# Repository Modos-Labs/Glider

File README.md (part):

# Glider

Open-source Eink monitor with an emphasis on low latency.

Note: This repo only contains the hardware design, the gateware running on the FPGA is my open-source [Caster EPDC](https://gitlab.com/zephray/Caster/) design. This README also contains information about the Caster as well.

This is a long document, containing not just information about this project, but also pretty much everything I know about Eink. Given it's a bit hard to gather information about Eink online, I think this is the right thing to do. Use the following table of contents to navigate around.

Eink is a registered trademark and brand of E Ink Corporation. All the contents provided in this repo are based on publicly available information online and original research. They are not endorsed by Eink in any way and they may contain errors and/ or inaccuracies. 

If you're interested in attaining a board, checkout the [product page for the Modos Paper Dev Kit on Crowd Supply](https://www.crowdsupply.com/modos-tech/modos-paper-monitor). For complete monitor ready to be used out-of-the-box, checkout the [product page for the Modos Flow on Crowd Supply](https://www.crowdsupply.com/modos-tech/modos-flow).

If you are interested in Eink or any other display technologies, I have a Discord server for that. Feel free to join: [https://discord.gg/rtT7euSHQS](https://discord.gg/rtT7euSHQS) . (This Discord server is also not endorsed by Eink or any other company. It's not a customer support server.) For Modos product support or other inqueries about Modos products, use [https://discord.gg/6ktE6VxSyh](https://discord.gg/6ktE6VxSyh).

## Quick Start

If you already have a Glider board/ kit: For board setup, flashing, development build loops, and display configuration, start with [USAGE.md](USAGE.md).

## Table of Contents 

- [Overview](#overview)
    - [Features](#features)
    - [Hardware](#hardware)
    - [Components](#components)
- [Eink Screens](#eink-screens)
    - [Basic Theory of Operation](#basic-theory-of-operation)
    - [Advantages and Disadvantages](#advantages-and-disadvantages)
    - [The Role of Eink Controller](#the-role-of-eink-controller)
    - [Screen Panel Types](#screen-panel-types)
    - [Using Screen with Integrated Controller](#using-screen-with-integrated-controller)
    - [Using Screen without Integrated Controller](#using-screen-without-integrated-controller)
    - [Understanding Waveform](#understanding-waveform)
    - [Greyscale Display](#greyscale-display)
    - [Color Display](#color-display)
    - [Dithering](#dithering)
    - [Eink Screen Generations](#eink-screen-generations)
- [Caster/ Glider Design](#design-of-caster-and-glider)
    - [Low Latency Drive](#low-latency-drive)
    - [Hybrid Greyscale Mode](#hybrid-greyscale-mode)
    - [Limitations](#limitations)
    - [Hardware Design Decisions]()
    - [Gateware Architecture](#gateware-architecture)
    - [Firmware Functions](#firmware-functions)
    - [Resources Utilization](#resources-utilization)
- [Building](#building)
    - [PCB](#pcb)
    - [FPGA Bitstream](#fpga-bitstream)
    - [MCU Firmware](#mcu-firmware)
    - [Flashing Board](#flashing-board)
    - [Compatible Screens](#compatible-screens)
- [References](#references)
- [License](#license)
- [Appendix](#appendix)
    - [Using Screens without Datasheet](#using-screens-without-datasheet)
    - [Screen List](#screen-list)

## Overview

### Features

- Complete solution for low-latency/ high-refresh-rate EPD monitor
- Supports electrophoretic display panels with parallel I/F (Eink(R), OED and DES)
- Supports both monochrome and color-filter-array (such as Kaleido(TM)) based color screen
- Extremely low processing delay of \<20 us
- Supports binary, 4-level grayscale, and 16-level grayscale output modes
- Latency-optimized binary and 4-level grayscale driving modes
- Hybrid automatic binary and 16-level grayscale driving mode
- Host software runtime controllable regional update and mode switching
- Hardware bayer dithering, blue-noise dithering, and error-diffusion dithering with no additional latency
- Controller takes standard HVsync signal input
- Board-level design supports USB-C (USB Type-C DisplayPort Alt Mode) and DVI input

### Hardware

- Xilinx(R) Spartan-6 LX16 FPGA running Caster
- DDR3-800 framebuffer memory
- Type-C DisplayPort Alt-Mode video input with onboard PTN3460 DP-LVDS bridge or
- DVI (via miniHDMI connector) video input with onboard ADV7611 decoder
- Epaper power supply with up to 1A peak current on +/-15V rail supporting large panels
- VCOM kick-back voltage measurement support
- On-board STM32H750 microcontroller for USB communication and firmware upgrade
- Up to 133MP/s processing rate with error-diffusion dithering enabled, >200MP/s when disabled

The board is designed with KiCad. You may need the latest stable version of KiCad to open the source file.

### Components

This repo hosts the PCB design and firmware source code. The RTL code is in a separate repo: [https://gitlab.com/zephray/Caster/](https://gitlab.com/zephray/Caster/).

## Eink Screens

Eink is the brand of a family of paper-like electrophoretic displays. The underlying technology is invented in the MIT Media Lab between 1995 and 1997 by Barrett Comiskey, J.D. Albert, and Joseph Jacobson. They later founded the E Ink Corporation to commercialize this technology.

Nowadays they are commonly used on e-readers and electronic shelf labels. You’ve probably seen them on Kindle, in stores, or maybe in some train stations as well.

| eReader/ Tablets | Electronic Shelf Label | Digital Signage |
|-|-|-|
|  |  |  |

(Source: https://www.eink.com/application, image copyright Eink corporation)

This section gives an overview of the electrophoretic displays, including the screen panels available and underlying technology. Note this project doesn't and can't support all electrophoretic screens. This documentation also solely focuses on using existing off-the-shelf screen panels rather than the physics or manufacturing process of one.

### Basic Theory of Operation

In the simplest form, you have charged particles with different colors, dispersed in some oil in some transparent container. By applying electric fields the particles can be moved up or down to produce either black or white, or a mixture of that.

(Source: https://www.eink.com/tech/detail/How_it_works , copyright Eink Corporation)

There are multiple technologies based on this basic concept, namely Eink’s micro-capsule display, SiPix (now acquired by Eink)’s micro-cup display, and WFT’s DES display. They differ in specific ways of confining the particles in containers, but otherwise very similar.

The pixels on the screen are typically arranged as a 2D array, driven with TFTs. The pixels are scanned/ driven periodically at a fixed refresh rate, typically ranging from 50Hz to 120Hz. Applying positive voltage on the pixel will typically drive the particles toward the white state while applying negative voltage will drive the particles towards the black state. This is similar to active matrix TN/IPS LCDs, which also use 2D TFT arrays and electrical fields for changing state. However, unlike LCDs, EPDs maintain their state after the electrical field is removed. So unlike LCDs which require continuous refreshing, the EPDs only need to be refreshed till the pixels are fully driven.

In terms of driving the screen panel, depending on the pixel value (1 or 0), each pixel would be driven either with a positive voltage or a negative voltage. A global counter can be used to count the frames elapsed and stop driving the pixels after a predefined period of time (for example, 100ms). Two framebuffers are typically used for determining if the pixel has changed color or not. If not, then the pixel does not need to be driven.

### Advantages and Disadvantages

In terms of display quality, EPDs are no match for modern IPS LCDs. The following is a comparison table of key parameters. The specific number would vary depending on the screen used but should be within the same ballpark.

| | Monochrome EPD | CFA-based Color EPD | Transmissive TFT IPS LCD | Reflective TFT TN LCD |
|-|-|-|-|-|
| Contrast Ratio | ~17:1 | ~14:1 | ~1000:1 | ~14:1 |
| Colors | 16 (Greyscale) | 4096 | 16M | 256 |
| Color Gamut | N/A | ~1.5% sRGB | ~99.9% sRGB | N/A |
| Reflectivity | ~45% | ~25% | N/A | ~15% |
| Response Time | ~150ms | ~150ms | ~10ms | ~15ms |

It has a few advantages. It reflects lights instead of emitting lights, so it generally consumes less power and can be used outdoors, etc. It’s also bistable, which means that it retains the image after the power has been removed. Personally, the biggest differentiating factor for me (author of this README) is that it looks like paper.

The image above shows a comparison between reflective TFT LCD (SHARP memory LCD in this case) and Eink. The LCD has a mirror-like texture which changes reflectivity drastically in different angles, while the Eink is more paper-like.

| ZBD LCD | Ch LCD | STN LCD |
|-|-|-|
|  |  |  |
| Bistable, reflective, high contrast, no greyscale, ~10s refresh | Bistable, reflective, lower contrast, up to 32 level greyscale, ~5s refresh | Volatile, reflective, lower contrast, up to 32 level greyscale, ~100ms response |

There are many other reflective or bistable display technologies. They are all interesting displays on their own, but none of them feels like paper (yet).

Overall, there is no single perfect display technology. Each has its own unique strength. Pick the right one for your project.

### The Role of Eink Controller

The Eink controller is in some ways similar to the display controller (DC/ CRTC) + timing controller (TCON) in a typical LCD-based system. It takes the raw image data and converts it to signals required to drive the screen.

To understand the actual work of an eink controller, start from the basic concept. The color of a pixel can be changed by applying positive or negative voltage for a finite period of time. From the controller’s perspective, depending on the current state of the pixel and the desired state of the pixel, there are 4 possibilities.

| Current State | Target State | Action |
|-|-|-|
| Black | Black | No operation |
| Black | White | Apply positive voltage |
| White | Black | Apply negative voltage |
| White | White | No operation |

The controller needs to store and maintain the screen state inside of its own buffer memory, so it would typically have a large on-chip SRAM or an off-chip SDRAM controller. The controller should also have a timer to ensure the screen doesn't get overdriven or underdriven.

The controller often uses the so-called "[waveform](#understanding-waveform)" to replace the action column of the previous table. Instead of hardcoding the action for state transition, the actions are stored into a look-up-table (LUT) which can be modified at runtime to allow higher flexibility.

Controllers may also offer more advanced features such as [dithering](#dithering) acceleration, multiple region updates, automatic LUT selection, etc.

### Screen Panel Types

As discussed in the previous section, an Eink screen needs to be coupled to an Eink controller to function. Aside from that, the screen also needs high-voltage drivers to drive the TFTs and the pixels. Virtually all E-paper panels use either COG (Chip-on-Glass) or TAB (Tape Auto Bonding) to integrate some chips onto the screen panel itself. Most of the screens available today can be divided into two categories based on whether or not the controller is integrated in:

Here is a non-exhaustive list of the types based on their size: (the size or resolution is not related to or limited by the type, it is just for a certain size, and the vendors tend to make them the same type.)

- Screens without controller: 4.3", 6.0", 7.8", 8.0", 9.7", 10.3", 13.3", 25.3", 31.2", 42"
- Screens with controller: 1.02", 1.54", 2.13", 2.6", 2.9", 3.71", 4.2", 5.65", 5.83", 7.5", 12.48"

One may notice that almost all e-readers/ e-ink cellphones use screens without controllers, while almost all e-ink electronic shelf labels (ESL) use screens with controllers. This gives some hints about the advantages and disadvantages of two types:

| | Without Controller | With Controller |
|-|-|-|
| System Cost | High. A dedicated controller or SoC with an integrated controller is usually required. Needs a dedicated power supply. | Low. Virtually any MCU could drive the screen directly, and the power supply is integrated in. |
| Greyscale Levels | Generally 16 (4bpp), up to 32 (5bpp) | Generally 2 (BW only) or 4 (2bpp), with some hack, up to 16 (4bpp) |
| Refresh Speed | Generally fast (100ms~300ms) for BW. Depends on the screen used and the system architecture | Generally fast (100ms~300ms) for BW if the partial refresh is enabled. Greyscales are much slower, BWR or BWY screens would be even slower.
| Total Update Latency | Generally the same as refresh time. Depends on the system architecture | Slow. Ranging from 100ms to several seconds based on the resolution. |

Please keep in mind the discussion is about off-the-shelf screens you can buy today. These tradeoffs do not necessarily come from the fact the controller is integrated or not.

Note that I mentioned the refresh speed and total update latency. They are different:

The refresh speed refers to the time it takes to start refreshing the screen: from starting to seeing screen changing, to the screen finish showing the new content.

The total update latency refers to the latency when the processor needs to update the screen, to the screen finish showing the new content. As you can see, this is the biggest issue for screens with controllers. This is the main reason why they are rarely used on e-readers cell phones or PC monitors.

This diagram illustrates the difference between the two. It should be noted that the screens without controllers have the flexibility to be driven quickly, but the system designer might not architect the system for low latency.

### Using Screen with Integrated Controller

Screens with integrated controllers have almost everything already integrated. Common display panels of this type only need a few external capacitors, inductors, and MOSFETs to support the integrated bipolar power supply circuit, then it could be hooked up to MCUs or MPUs using common interfaces like SPI or I2C. There are a lot of driving boards and examples of these screens available online.

To be expanded (TODO)

### Using Screen without Integrated Controller

This could get complicated. Note I used a lot of "generally" in the previous comparison table because there are many things one could do to drive them. Some of them would certainly impact the performance. The main issue here is the controller chip. There are three solutions to drive these screens:

- Using a dedicated controller chip to drive the screen
- Using an SoC that has an integrated controller
- Using a fast MCU/SoC to emulate the controller with GPIO (software timing controller)

Then, again here is a comparison between them:

| | Specialized controller chip | SoC with integrated controller | MCU + Software TCON |
|-|-|-|-|
| Resolution | UXGA+ | UXGA+ | Limited by MCU RAM. Up to XGA with SRAM, UXGA with PSRAM, UXGA+ with DDR |
| Greyscale | Up to 32 | Up to 32 | Up to 32 |
| Partial Update | Yes | Yes | Yes |
| Total Update Latency | Depends. Could be very close to refresh speed, could be slow like screens with controller | Same as refresh speed | Same as refresh speed if data is internally generated (not streaming from an external device such as a PC) |
| Suitable Applications | IoT devices, E-readers, cellphones, E-ink monitors. possibly E-ink laptops | Advanced IoT devices, E-readers, cellphones, E-ink typewriters, possibly lower performance E-ink laptops | When using MCU: IoT devices, large ESLs, simple DIY E-readers. When using MPU: Same as SoC with integrated controller |

When using a dedicated controller, it could accept data from external devices. This allows it to be used in various different types of applications. Ranging from IoT devices, and ESLs, to PC monitors with relatively fast refresh rate and low latency.

When using SoC or MCU, the display content is generated by the SoC or MCU itself, which ultimately is limited by the capability of the SoC or MCU. Given the current SoCs with E-ink display controllers are usually limited in performance, the application is limited. The same goes for MCU, it does what an MCU could do. You could find ways to stream video data into SoC or MCUs by using USB, camera interface, WiFi, etc., but this might not be optimal.

#### Existing Solutions

- Specialized controller chip
    - Closed-source
        - EPSON S1D13xxx: Widely used EPD controller in early E-readers. Proprietary, no documents available. Probably EOL.
        - IT8951: Used on the waveshare EPD Hat. Documents are available. It works with large EPDs up to 2048x2048. The drawback is the speed as the interface between processor and IT8951 could be slow. This is similar to the situation on screens with integrated controller
        - T1000: Also known as IT8957, upgraded model of IT8951. It supports even higher resolution. It features a higher speed MIPI DSI interface to mitigate the slow speed of IT8951. Features an integrated OpenRISC based processor.
        - T2000: Upgraded model of T1000.
        - T2001: Also known as IT8959. Features an integrated RISC-V based processor. Works with large EPDs up to 2560x1920. Supports SPI, RGB, MIPI DSI interface.
        - Waveshare HDMI driver board: FPGA-based controller. Closed source but easily purchasable, could be integrated into larger projects as a module.
    - Open-source
        - This project (Caster + Glider): FPGA-based controller, multiple update modes, ultra-low latency processing, and wide range of screen support.
        - https://hackaday.io/project/21607-paperback-a-desktop-epaper-monitor: FPGA-based controller. However, doesn't support partial update mode and slower speed.
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
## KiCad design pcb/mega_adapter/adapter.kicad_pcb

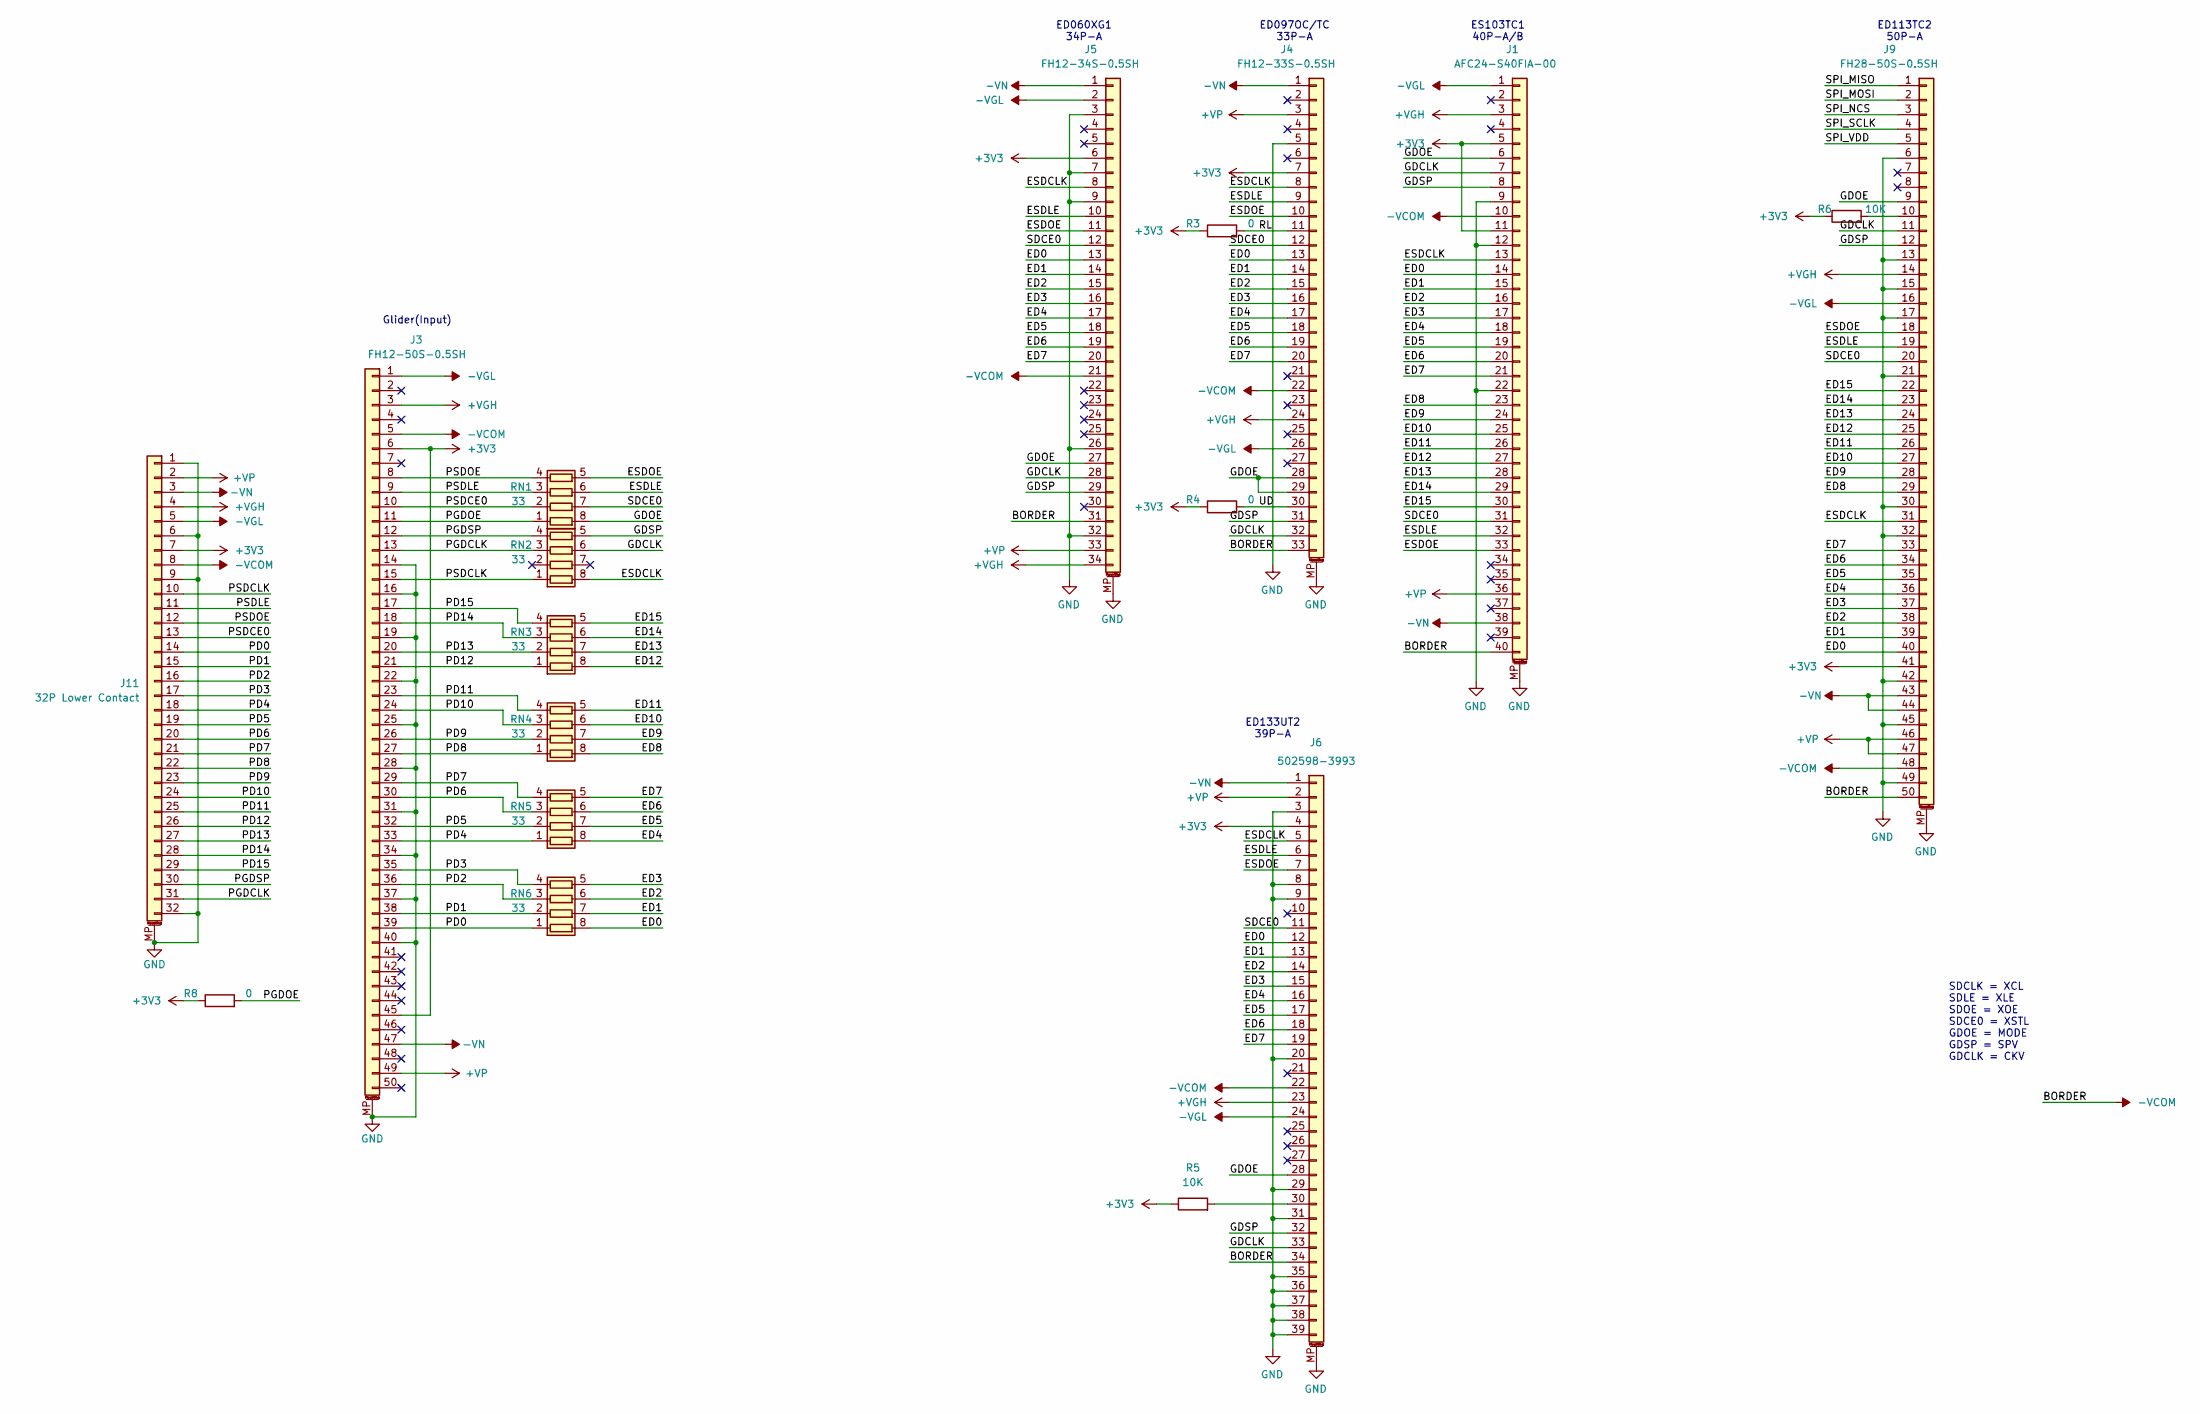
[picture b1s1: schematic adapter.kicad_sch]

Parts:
J1: AFC24-S40FIA-00; Omron_XF2M-4015-1A_1x40-1MP_P0.5mm_Horizontal
J3: FH12-50S-0.5SH; Hirose_FH12-50S-0.5SH_1x50-1MP_P0.50mm_Horizontal_Mirrored
J4: FH12-33S-0.5SH; Hirose_FH12-33S-0.5SH_1x33-1MP_P0.50mm_Horizontal
J5: FH12-34S-0.5SH; Hirose_FH12-34S-0.5SH_1x34-1MP_P0.50mm_Horizontal
J6: 502598-3993; Molex_5025983993; LCSC 609-10064555-392120HLFCT-ND
J9: FH28-50S-0.5SH; Hirose_FH12-50S-0.5SH_1x50-1MP_P0.50mm_Horizontal
J11: 32P Lower Contact; Hirose_FH12-32S-0.5SH_1x32-1MP_P0.50mm_Horizontal_Mirrored
R3, R4, R8: 0; R_0402_1005Metric
R5, R6: 10K; R_0402_1005Metric
RN1, RN2, RN3, RN4, RN5, RN6: 33; R_Array_Convex_4x0402

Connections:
+3V3: J1.5, J1.11, J3.6, J3.45, J4.7, J5.6, J6.4, J9.41, J11.7, R3.1, R4.1, R5.1, R6.1, R8.1
+VGH: J1.3, J3.3, J4.24, J5.34, J6.23, J9.14, J11.4
+VP: J1.36, J3.49, J4.3, J5.33, J6.2, J9.46, J9.47, J11.2
-VCOM: J1.10, J1.40, J3.5, J4.22, J4.33, J5.21, J5.31, J6.22, J6.34, J9.48, J9.50, J11.8
-VGL: J1.1, J3.1, J4.26, J5.2, J6.24, J9.16, J11.5
-VN: J1.38, J3.47, J4.1, J5.1, J6.1, J9.43, J9.44, J11.3
/ED0: J1.14, J4.13, J5.13, J6.12, J9.40, RN6.8 (R1.2)
/ED1: J1.15, J4.14, J5.14, J6.13, J9.39, RN6.7 (R2.2)
/ED2: J1.16, J4.15, J5.15, J6.14, J9.38, RN6.6 (R3.2)
/ED3: J1.17, J4.16, J5.16, J6.15, J9.37, RN6.5 (R4.2)
/ED4: J1.18, J4.17, J5.17, J6.16, J9.36, RN5.8 (R1.2)
/ED5: J1.19, J4.18, J5.18, J6.17, J9.35, RN5.7 (R2.2)
/ED6: J1.20, J4.19, J5.19, J6.18, J9.34, RN5.6 (R3.2)
/ED7: J1.21, J4.20, J5.20, J6.19, J9.33, RN5.5 (R4.2)
/ED8: J1.23, J9.29, RN4.8 (R1.2)
/ED9: J1.24, J9.28, RN4.7 (R2.2)
/ED10: J1.25, J9.27, RN4.6 (R3.2)
/ED11: J1.26, J9.26, RN4.5 (R4.2)
/ED12: J1.27, J9.25, RN3.8 (R1.2)
/ED13: J1.28, J9.24, RN3.7 (R2.2)
/ED14: J1.29, J9.23, RN3.6 (R3.2)
/ED15: J1.30, J9.22, RN3.5 (R4.2)
/ESDCLK: J1.13, J4.8, J5.8, J6.5, J9.31, RN2.8 (R1.2)
/ESDLE: J1.32, J4.9, J5.10, J6.6, J9.19, RN1.6 (R3.2)
/ESDOE: J1.33, J4.10, J5.11, J6.7, J9.18, RN1.5 (R4.2)
/GDCLK: J1.7, J4.32, J5.28, J6.33, J9.11, RN2.6 (R3.2)
/GDOE: J1.6, J4.28, J4.29, J5.27, J6.28, J9.9, RN1.8 (R1.2)
/GDSP: J1.8, J4.31, J5.29, J6.32, J9.12, RN2.5 (R4.2)
/PD0: J3.39, J11.14, RN6.1 (R1.1)
/PD1: J3.38, J11.15, RN6.2 (R2.1)
/PD2: J3.36, J11.16, RN6.3 (R3.1)
/PD3: J3.35, J11.17, RN6.4 (R4.1)
/PD4: J3.33, J11.18, RN5.1 (R1.1)
/PD5: J3.32, J11.19, RN5.2 (R2.1)
/PD6: J3.30, J11.20, RN5.3 (R3.1)
/PD7: J3.29, J11.21, RN5.4 (R4.1)
/PD8: J3.27, J11.22, RN4.1 (R1.1)
/PD9: J3.26, J11.23, RN4.2 (R2.1)
/PD10: J3.24, J11.24, RN4.3 (R3.1)
/PD11: J3.23, J11.25, RN4.4 (R4.1)
/PD12: J3.21, J11.26, RN3.1 (R1.1)
/PD13: J3.20, J11.27, RN3.2 (R2.1)
/PD14: J3.18, J11.28, RN3.3 (R3.1)
/PD15: J3.17, J11.29, RN3.4 (R4.1)
/PGDCLK: J3.13, J11.31, RN2.3 (R3.1)
/PGDOE: J3.11, R8.2, RN1.1 (R1.1)
/PGDSP: J3.12, J11.30, RN2.4 (R4.1)
/PSDCE0: J3.10, J11.13, RN1.2 (R2.1)
/PSDCLK: J3.15, J11.10, RN2.1 (R1.1)
/PSDLE: J3.9, J11.11, RN1.3 (R3.1)
/PSDOE: J3.8, J11.12, RN1.4 (R4.1)
/RL: J4.11, R3.2
/SDCE0: J1.31, J4.12, J5.12, J6.11, J9.20, RN1.7 (R2.2)
/SPI_MISO: J9.1
/SPI_MOSI: J9.2
/SPI_NCS: J9.3
/SPI_SCLK: J9.4
/SPI_VDD: J9.5
/UD: J4.30, R4.2
GND: J1.9, J1.12, J1.22, J1.MP (MountPin), J3.14, J3.16, J3.19, J3.22, J3.25, J3.28, J3.31, J3.34, J3.37, J3.40, J3.MP (MountPin), J4.5, J4.MP (MountPin), J5.3, J5.7, J5.9, J5.26, J5.32, J5.MP (MountPin), J6.3, J6.8, J6.9, J6.20, J6.29, J6.31, J6.35, J6.36, J6.37, J6.38, J6.39, J6.MP (MountPin), J9.6, J9.13, J9.15, J9.17, J9.21, J9.30, J9.32, J9.42, J9.45, J9.49, J9.MP (MountPin), J11.1, J11.6, J11.9, J11.32, J11.MP (MountPin)
unnamed: J6.30, R5.2
unnamed: J9.10, R6.2

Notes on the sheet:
ED133UT2 39P-A
ED060XG1 34P-A
ED113TC2 50P-A
Glider(Input)
ES103TC1 40P-A/B
ED097OC/TC 33P-A
SDCLK = XCL SDLE = XLE SDOE = XOE SDCE0 = XSTL GDOE = MODE GDSP = SPV GDCLK = CKV

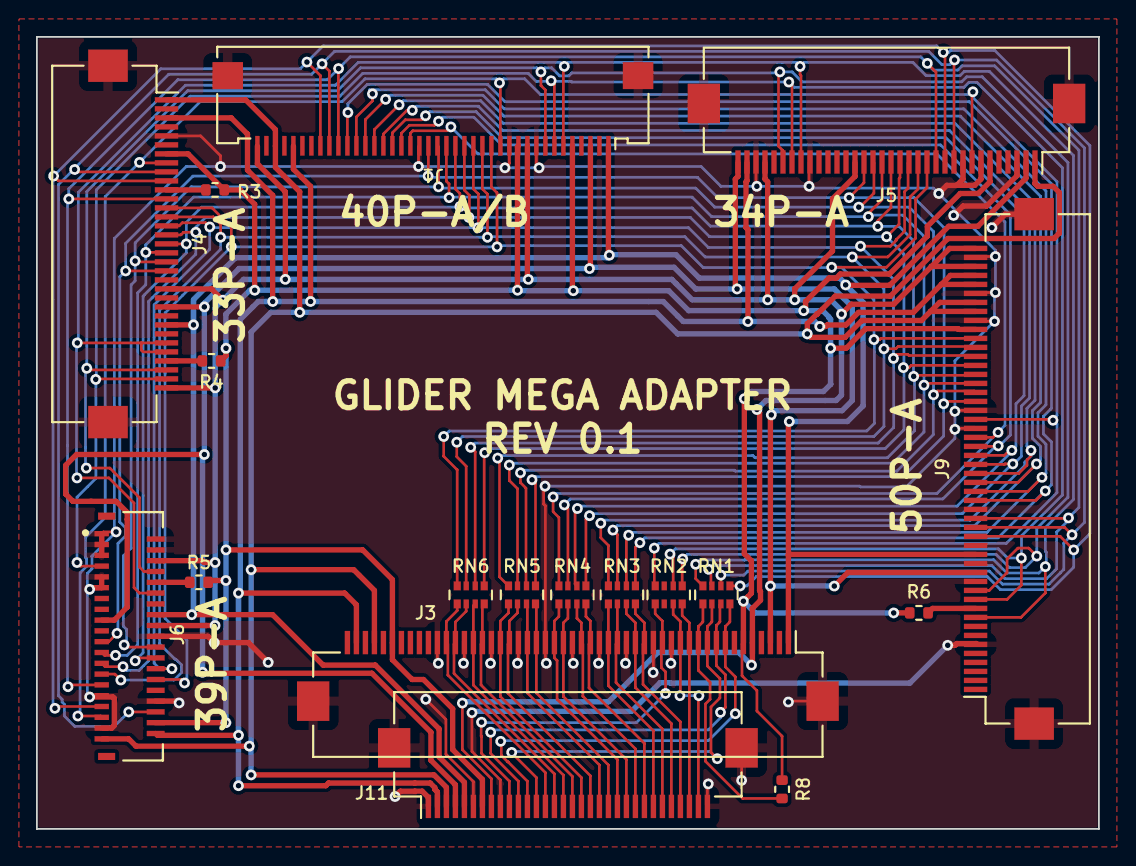
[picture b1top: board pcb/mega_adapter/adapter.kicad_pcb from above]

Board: 2 copper layers, 59.0 x 44.0 mm, 18 parts (0 on the bottom side), 57 nets.

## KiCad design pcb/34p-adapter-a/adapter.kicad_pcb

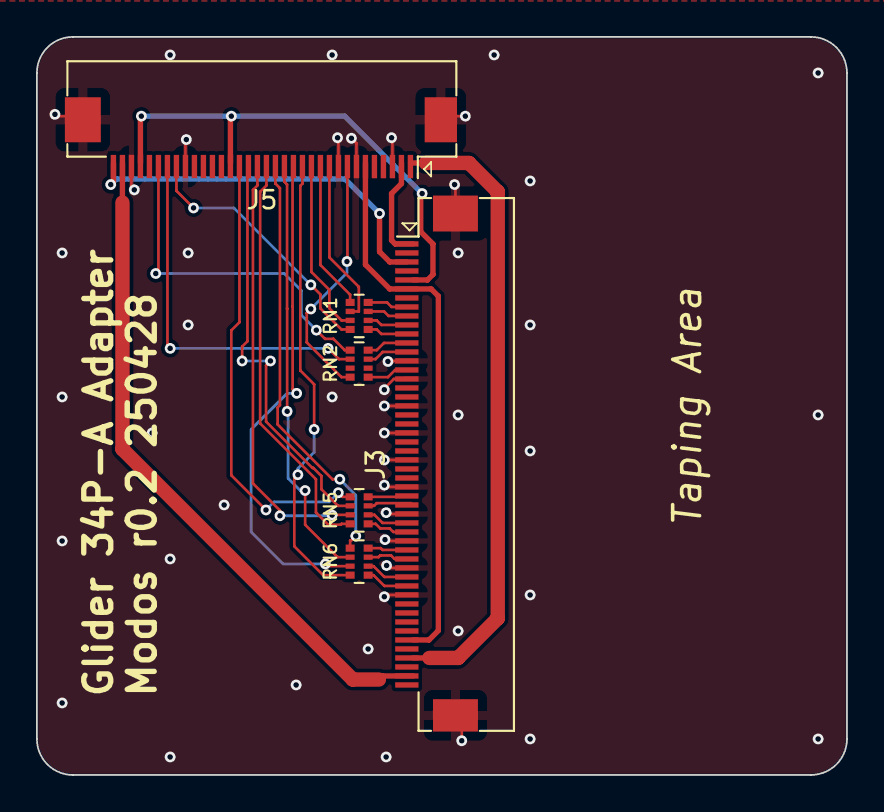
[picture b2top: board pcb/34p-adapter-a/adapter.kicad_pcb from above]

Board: 2 copper layers, 45.0 x 41.0 mm, 6 parts (0 on the bottom side), 37 nets.

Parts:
J3: FH12-50S-0.5SH; Xunpu_FPC-05F-50PH20_1x50-1MP_P0.50mm_Horizontal_Mirrored
J5: FH12-34S-0.5SH; Xunpu_FPC-05F-34PH20_1x34-1MP_P0.50mm_Horizontal
RN1, RN2, RN5, RN6: 33; R_Array_Convex_4x0402

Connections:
+3V3: J3.6, J3.45, J5.6
+VGH: J3.3, J5.34
+VP: J3.49, J5.33
-VCOM: J3.5, J5.21, J5.31
-VGL: J3.1, J5.2
-VN: J3.47, J5.1
/ED0: J5.13, RN6.8 (R1.2)
/ED1: J5.14, RN6.7 (R2.2)
/ED2: J5.15, RN6.6 (R3.2)
/ED3: J5.16, RN6.5 (R4.2)
/ED4: J5.17, RN5.8 (R1.2)
/ED5: J5.18, RN5.7 (R2.2)
/ED6: J5.19, RN5.6 (R3.2)
/ED7: J5.20, RN5.5 (R4.2)
/ESDCLK: J5.8, RN2.8 (R1.2)
/ESDLE: J5.10, RN1.6 (R3.2)
/ESDOE: J5.11, RN1.5 (R4.2)
/GDCLK: J5.28, RN2.6 (R3.2)
/GDOE: J5.27, RN1.8 (R1.2)
/GDSP: J5.29, RN2.5 (R4.2)
/PD0: J3.39, RN6.1 (R1.1)
/PD1: J3.38, RN6.2 (R2.1)
/PD2: J3.36, RN6.3 (R3.1)
/PD3: J3.35, RN6.4 (R4.1)
/PD4: J3.33, RN5.1 (R1.1)
/PD5: J3.32, RN5.2 (R2.1)
/PD6: J3.30, RN5.3 (R3.1)
/PD7: J3.29, RN5.4 (R4.1)
/PGDCLK: J3.13, RN2.3 (R3.1)
/PGDOE: J3.11, RN1.1 (R1.1)
/PGDSP: J3.12, RN2.4 (R4.1)
/PSDCE0: J3.10, RN1.2 (R2.1)
/PSDCLK: J3.15, RN2.1 (R1.1)
/PSDLE: J3.9, RN1.3 (R3.1)
/PSDOE: J3.8, RN1.4 (R4.1)
/SDCE0: J5.12, RN1.7 (R2.2)
GND: J3.14, J3.16, J3.19, J3.22, J3.25, J3.28, J3.31, J3.34, J3.37, J3.40, J3.MP (MountPin), J5.3, J5.7, J5.9, J5.26, J5.32, J5.MP (MountPin)

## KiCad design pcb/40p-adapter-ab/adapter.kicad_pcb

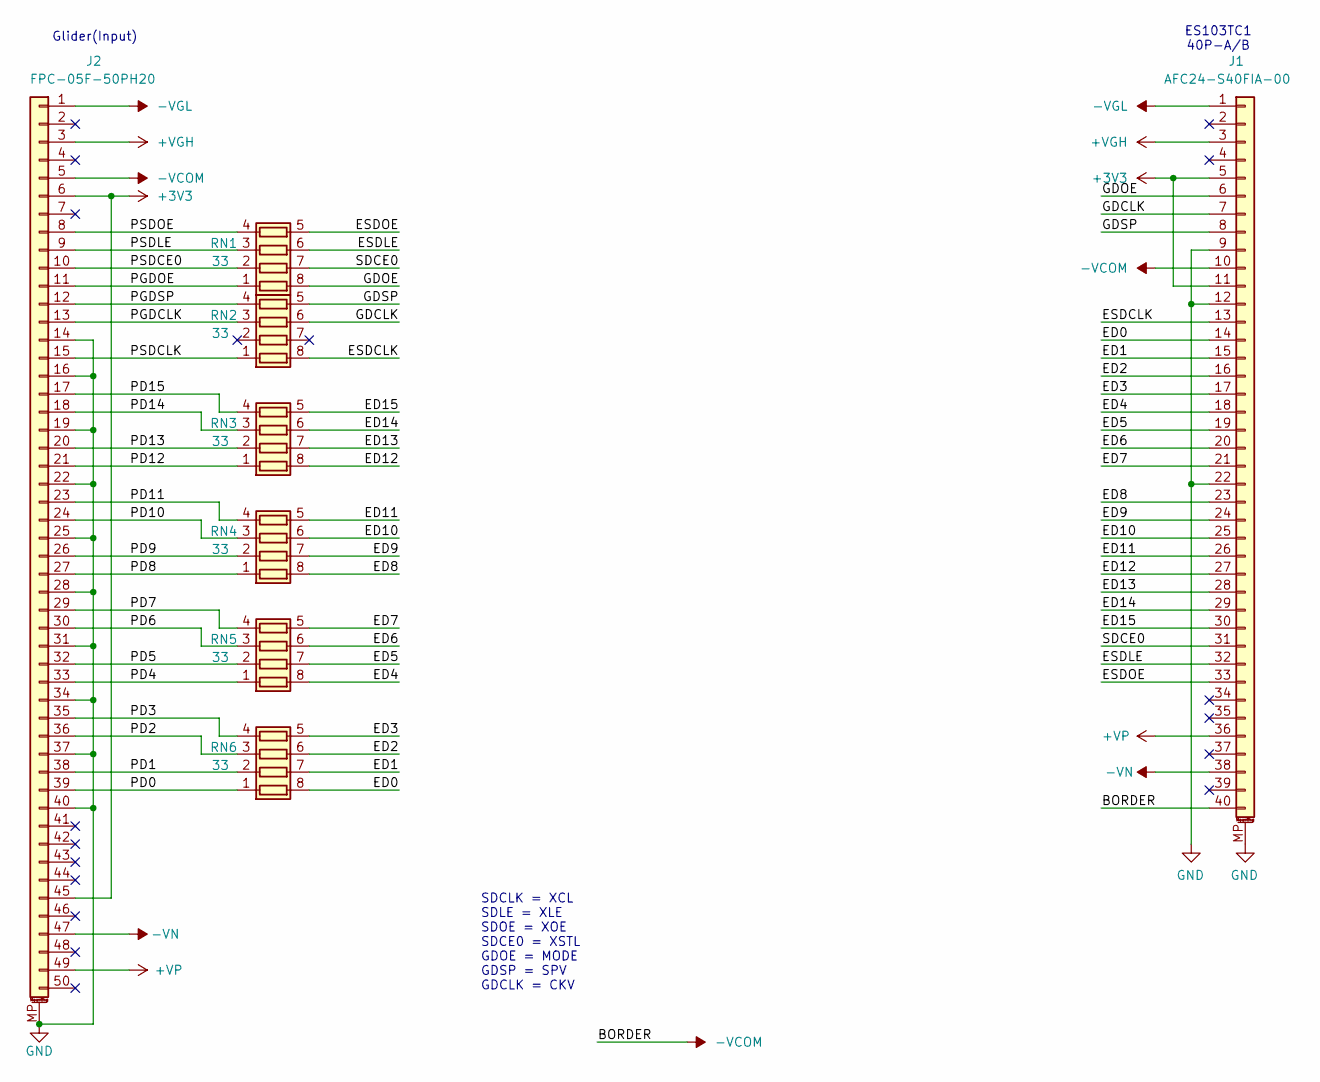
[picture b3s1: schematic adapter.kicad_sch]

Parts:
J1: AFC24-S40FIA-00; Omron_XF2M-4015-1A_1x40-1MP_P0.5mm_Horizontal
J2: FPC-05F-50PH20; Xunpu_FPC-05F-50PH20_1x50-1MP_P0.50mm_Horizontal_Mirrored
RN1, RN2, RN3, RN4, RN5, RN6: 33; R_Array_Convex_4x0402

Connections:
+3V3: J1.5, J1.11, J2.6, J2.45
+VGH: J1.3, J2.3
+VP: J1.36, J2.49
-VCOM: J1.10, J1.40, J2.5
-VGL: J1.1, J2.1
-VN: J1.38, J2.47
/ED0: J1.14, RN6.8 (R1.2)
/ED1: J1.15, RN6.7 (R2.2)
/ED2: J1.16, RN6.6 (R3.2)
/ED3: J1.17, RN6.5 (R4.2)
/ED4: J1.18, RN5.8 (R1.2)
/ED5: J1.19, RN5.7 (R2.2)
/ED6: J1.20, RN5.6 (R3.2)
/ED7: J1.21, RN5.5 (R4.2)
/ED8: J1.23, RN4.8 (R1.2)
/ED9: J1.24, RN4.7 (R2.2)
/ED10: J1.25, RN4.6 (R3.2)
/ED11: J1.26, RN4.5 (R4.2)
/ED12: J1.27, RN3.8 (R1.2)
/ED13: J1.28, RN3.7 (R2.2)
/ED14: J1.29, RN3.6 (R3.2)
/ED15: J1.30, RN3.5 (R4.2)
/ESDCLK: J1.13, RN2.8 (R1.2)
/ESDLE: J1.32, RN1.6 (R3.2)
/ESDOE: J1.33, RN1.5 (R4.2)
/GDCLK: J1.7, RN2.6 (R3.2)
/GDOE: J1.6, RN1.8 (R1.2)
/GDSP: J1.8, RN2.5 (R4.2)
/PD0: J2.39, RN6.1 (R1.1)
/PD1: J2.38, RN6.2 (R2.1)
/PD2: J2.36, RN6.3 (R3.1)
/PD3: J2.35, RN6.4 (R4.1)
/PD4: J2.33, RN5.1 (R1.1)
/PD5: J2.32, RN5.2 (R2.1)
/PD6: J2.30, RN5.3 (R3.1)
/PD7: J2.29, RN5.4 (R4.1)
/PD8: J2.27, RN4.1 (R1.1)
/PD9: J2.26, RN4.2 (R2.1)
/PD10: J2.24, RN4.3 (R3.1)
/PD11: J2.23, RN4.4 (R4.1)
/PD12: J2.21, RN3.1 (R1.1)
/PD13: J2.20, RN3.2 (R2.1)
/PD14: J2.18, RN3.3 (R3.1)
/PD15: J2.17, RN3.4 (R4.1)
/PGDCLK: J2.13, RN2.3 (R3.1)
/PGDOE: J2.11, RN1.1 (R1.1)
/PGDSP: J2.12, RN2.4 (R4.1)
/PSDCE0: J2.10, RN1.2 (R2.1)
/PSDCLK: J2.15, RN2.1 (R1.1)
/PSDLE: J2.9, RN1.3 (R3.1)
/PSDOE: J2.8, RN1.4 (R4.1)
/SDCE0: J1.31, RN1.7 (R2.2)
GND: J1.9, J1.12, J1.22, J1.MP (MountPin), J2.14, J2.16, J2.19, J2.22, J2.25, J2.28, J2.31, J2.34, J2.37, J2.40, J2.MP (MountPin)

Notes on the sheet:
Glider(Input)
ES103TC1 40P-A/B
SDCLK = XCL SDLE = XLE SDOE = XOE SDCE0 = XSTL GDOE = MODE GDSP = SPV GDCLK = CKV

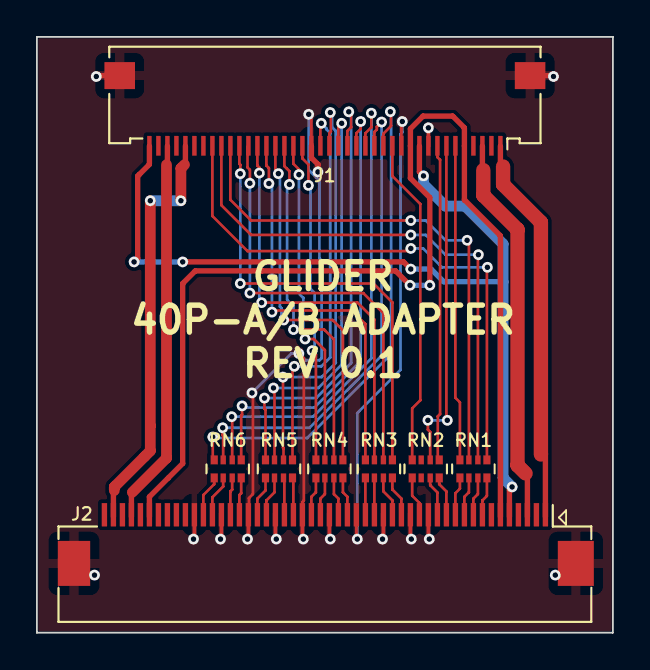
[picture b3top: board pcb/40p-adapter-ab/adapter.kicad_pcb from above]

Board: 2 copper layers, 32.0 x 33.1 mm, 8 parts (0 on the bottom side), 53 nets.

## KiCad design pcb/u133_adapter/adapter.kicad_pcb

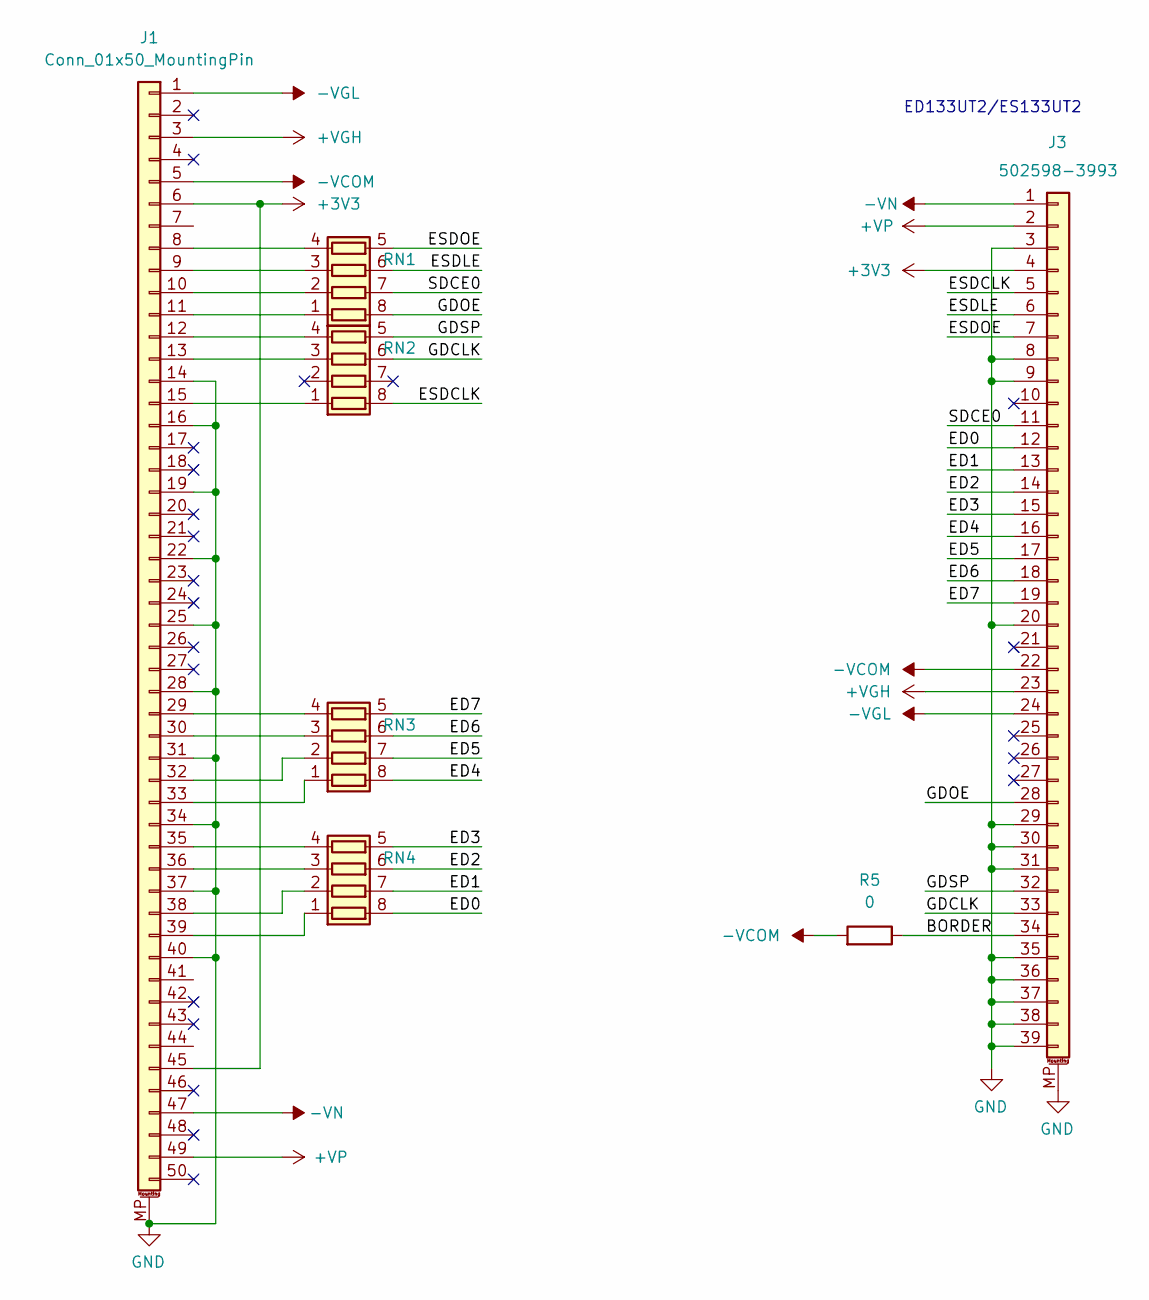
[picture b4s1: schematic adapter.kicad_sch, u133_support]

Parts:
J1: Conn_01x50_MountingPin; Xunpu_FPC-05F-50PH20_1x50-1MP_P0.50mm_Horizontal_Mirrored
J3: 502598-3993; Molex_5025983993; LCSC 609-10064555-392120HLFCT-ND
R5: 0; R_0402_1005Metric
RN1, RN2, RN3, RN4: 33R / 4D02WGF330JTCE; R_Array_Convex_4x0402

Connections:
+3V3: J1.6, J1.45, J3.4
+VGH: J1.3, J3.23
+VP: J1.49, J3.2
-VCOM: J1.5, J3.22, R5.2
-VGL: J1.1, J3.24
-VN: J1.47, J3.1
/BORDER: J3.34, R5.1
/ED0: J3.12, RN4.8 (R1.2)
/ED1: J3.13, RN4.7 (R2.2)
/ED2: J3.14, RN4.6 (R3.2)
/ED3: J3.15, RN4.5 (R4.2)
/ED4: J3.16, RN3.8 (R1.2)
/ED5: J3.17, RN3.7 (R2.2)
/ED6: J3.18, RN3.6 (R3.2)
/ED7: J3.19, RN3.5 (R4.2)
/ESDCLK: J3.5, RN2.8 (R1.2)
/ESDLE: J3.6, RN1.6 (R3.2)
/ESDOE: J3.7, RN1.5 (R4.2)
/GDCLK: J3.33, RN2.6 (R3.2)
/GDOE: J3.28, RN1.8 (R1.2)
/GDSP: J3.32, RN2.5 (R4.2)
/SDCE0: J3.11, RN1.7 (R2.2)
GND: J1.14, J1.16, J1.19, J1.22, J1.25, J1.28, J1.31, J1.34, J1.37, J1.40, J1.MP (MountPin), J3.3, J3.8, J3.9, J3.20, J3.29, J3.30, J3.31, J3.35, J3.36, J3.37, J3.38, J3.39, J3.MP (MountPin)
unnamed: J1.8, RN1.4 (R4.1)
unnamed: J1.9, RN1.3 (R3.1)
unnamed: J1.10, RN1.2 (R2.1)
unnamed: J1.11, RN1.1 (R1.1)
unnamed: J1.12, RN2.4 (R4.1)
unnamed: J1.13, RN2.3 (R3.1)
unnamed: J1.15, RN2.1 (R1.1)
unnamed: J1.29, RN3.4 (R4.1)
unnamed: J1.30, RN3.3 (R3.1)
unnamed: J1.32, RN3.2 (R2.1)
unnamed: J1.33, RN3.1 (R1.1)
unnamed: J1.35, RN4.4 (R4.1)
unnamed: J1.36, RN4.3 (R3.1)
unnamed: J1.38, RN4.2 (R2.1)
unnamed: J1.39, RN4.1 (R1.1)

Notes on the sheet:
ED133UT2/ES133UT2

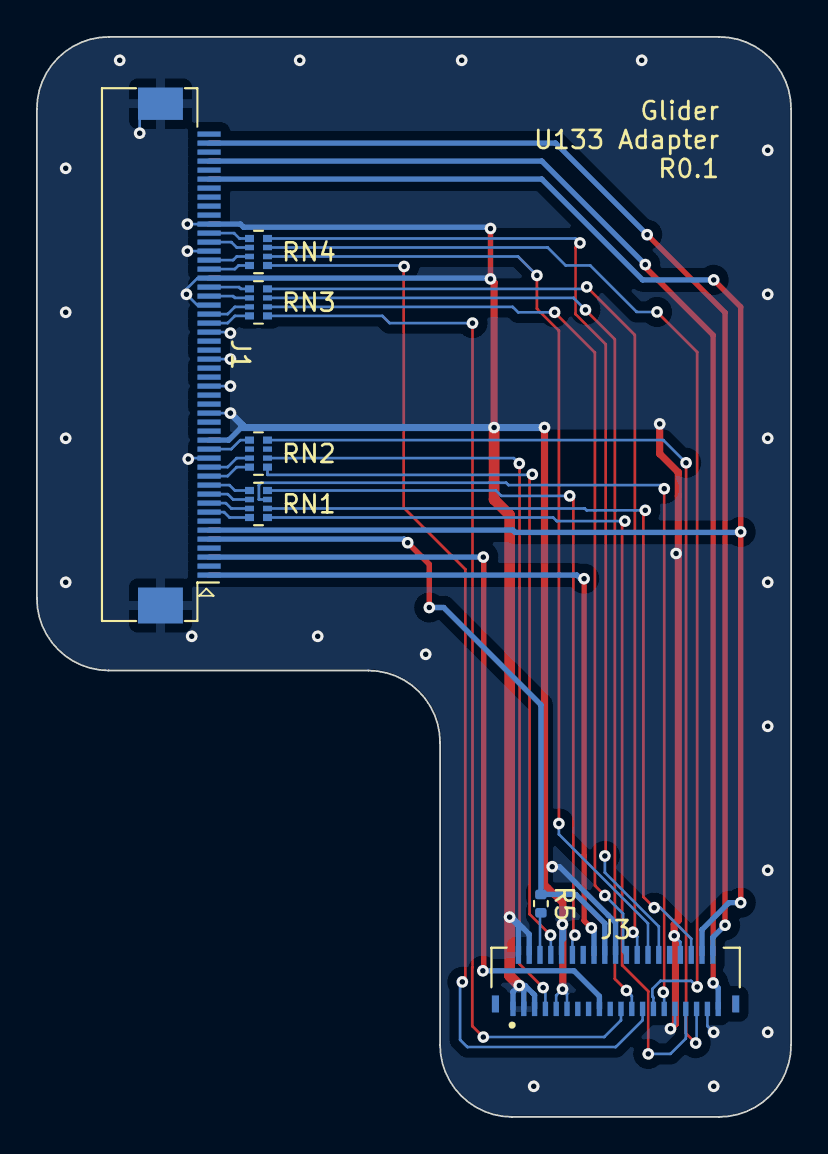
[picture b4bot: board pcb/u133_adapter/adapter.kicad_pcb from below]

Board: 2 copper layers, 41.9 x 60.0 mm, 7 parts (7 on the bottom side), 38 nets.

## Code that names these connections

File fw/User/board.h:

//
// Grimoire
// Copyright 2025 Wenting Zhang
//
// Permission is hereby granted, free of charge, to any person obtaining a copy
// of this software and associated documentation files (the "Software"), to deal
// in the Software without restriction, including without limitation the rights
// to use, copy, modify, merge, publish, distribute, sublicense, and/or sell
// copies of the Software, and to permit persons to whom the Software is
// furnished to do so, subject to the following conditions:
//
// The above copyright notice and this permission notice shall be included in
// all copies or substantial portions of the Software.
//
// THE SOFTWARE IS PROVIDED "AS IS", WITHOUT WARRANTY OF ANY KIND, EXPRESS OR
// IMPLIED, INCLUDING BUT NOT LIMITED TO THE WARRANTIES OF MERCHANTABILITY,
// FITNESS FOR A PARTICULAR PURPOSE AND NONINFRINGEMENT. IN NO EVENT SHALL THE
// AUTHORS OR COPYRIGHT HOLDERS BE LIABLE FOR ANY CLAIM, DAMAGES OR OTHER
// LIABILITY, WHETHER IN AN ACTION OF CONTRACT, TORT OR OTHERWISE, ARISING FROM,
// OUT OF OR IN CONNECTION WITH THE SOFTWARE OR THE USE OR OTHER DEALINGS IN THE
// SOFTWARE.
//
#pragma once

#include "pal_i2c.h"

#define LED_GRN         GPIOE, GPIO_PIN_0
#define LED_RED         GPIOE, GPIO_PIN_1

#define BTNCNT          3
#define BTN1            GPIOE, GPIO_PIN_4
#define BTN2            GPIOB, GPIO_PIN_5
#define BTN3            GPIOE, GPIO_PIN_3

#define BTN_PRESSED_LEVEL   1 // Active high

#define FPGA_CS         GPIOB, GPIO_PIN_12
#define FPGA_PROG       GPIOC, GPIO_PIN_10
#define FPGA_DONE       GPIOC, GPIO_PIN_11
#define FPGA_SUSP       GPIOC, GPIO_PIN_12

#define DP_PDN          GPIOD, GPIO_PIN_3
#define DP_HPD          GPIOD, GPIO_PIN_7
#define DEC_RST         GPIOD, GPIO_PIN_6

#define TYPEC_ORI       GPIOA, GPIO_PIN_10
#define TCPC_INT        GPIOA, GPIO_PIN_15

#define EPD_PWREN       GPIOE, GPIO_PIN_11
#define EPD_POSEN       GPIOE, GPIO_PIN_12
#define EPD_THROT       GPIOD, GPIO_PIN_2

#define FL_EN           GPIOE, GPIO_PIN_15

#define VCOM_MEN        GPIOA, GPIO_PIN_2
#define VCOM_EN         GPIOA, GPIO_PIN_3

#define FPGA_SPI        &hspi2

#define PTN3460_I2C     &pi2c1
#define ADV7611_I2C     &pi2c1
#define FUSB302_I2C     &pi2c1
#define INA3221_I2C     &pi2c1

#define TYPEC_MB_ORI_INV    0
#define TYPEC_AUX_ORI_INV   0

#define PTN3460_I2C_ADDR    (0x60)
#define ADV7611_I2C_ADDR    (0x4C)
#define FUSB302_I2C_ADDR    (0x22)
#define INA3221_0_I2C_ADDR  (0x40)
#define INA3221_1_I2C_ADDR  (0x41)
#define INA3221_2_I2C_ADDR  (0x42)

// ADV7611 Sub addresses, make sure they don't conflict with anything else!
#define CEC_I2C_ADDR        (0x3F) // Default 0x40(0x80)
#define INFOFRAME_I2C_ADDR  (0x3E) // Default 0x3E(0x7C)
#define DPLL_I2C_ADDR       (0x26) // Default 0x26(0x4C)
#define KSV_I2C_ADDR        (0x32) // Default 0x32(0x64)
#define EDID_I2C_ADDR       (0x36) // Default 0x36(0x6C)
#define HDMI_I2C_ADDR       (0x34) // Default 0x34(0x68)
#define CP_I2C_ADDR         (0x23) // Default 0x22(0x44)

// For now, these resources are not shared among multiple threads, do not protect them
extern SPI_HandleTypeDef hspi2;
extern ADC_HandleTypeDef hadc1;
extern DAC_HandleTypeDef hdac1;
extern QSPI_HandleTypeDef hqspi;
extern TIM_HandleTypeDef htim1;

// GPIO operations are atomic, no need to protect
#define gpio_put        HAL_GPIO_WritePin
#define gpio_get        HAL_GPIO_ReadPin
#define sleep_ms(x)     vTaskDelay(pdMS_TO_TICKS(x))

#define spi_send(spi, buf, size) \
    HAL_SPI_Transmit(spi, buf, size, HAL_MAX_DELAY)
#define spi_send_dma(spi, buf, size) \
    HAL_SPI_Transmit_DMA(spi, buf, size)
#define spi_send_recv(spi, txbuf, rxbuf, size) \
    HAL_SPI_TransmitReceive(spi, txbuf, rxbuf, size, HAL_MAX_DELAY)

#define board_get_uid   HAL_GetUIDw0

size_t board_usb_get_serial(uint16_t desc_str1[], size_t max_chars);
void board_switch_spi_freq(SPI_HandleTypeDef *spi, uint32_t target);
void board_late_init(void); // Initialization only after RTOS has started
void sleep_us(uint32_t x);
void spi_wait_dma_complete(SPI_HandleTypeDef *spi);

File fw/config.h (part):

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#define TYPEC_MB_ORI_INV    1
#define TYPEC_AUX_ORI_INV   1

#define I2C_SDA     0
#define I2C_SCL     1

#define TCPC_I2C i2c0

#define FPGA_CS     12
#define FPGA_MOSI   13
#define FPGA_MISO   14
#define FPGA_SCLK   15
#define FPGA_PROG   17
#define FPGA_DONE   18
#define FPGA_SUSP   19

#define PTN3460_I2C         (i2c0)
#define PTN3460_HPD_PIN     (8)
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#define TYPEC_MB_ORI_INV    0
#define TYPEC_AUX_ORI_INV   1

#define I2C_SDA     2
#define I2C_SCL     3

#define TCPC_I2C i2c1

#define FPGA_CS     13
#define FPGA_MOSI   15
#define FPGA_MISO   12
#define FPGA_SCLK   14
#define FPGA_PROG   17
#define FPGA_DONE   18
#define FPGA_SUSP   19

#define PTN3460_I2C         (i2c1)
#define PTN3460_HPD_PIN     (7)
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
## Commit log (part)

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2022-03-05 - Initial commit
2022-06-08 doc: update readme and change log
2022-07-04 pcb: r0p4
2022-07-04 pcb: 39p adapter for ed133/es133ut screens
2022-09-04 fw: initial controller fw
2022-11-21 pcb: r0p5
2023-03-04 fw: power, fpga handling, fix ptn3460 params
2023-06-26 pcb: r0p6
2023-12-08 Add GPIO controlled power supply support
2023-12-08 Define EDID from config macros
2023-12-10 Add missing include
2023-12-27 Initial design of lite version
2023-12-27 Lite version r0p1
2024-01-10 Fix PCB thickness; add initial case design for lite version
2024-01-16 Update README.md with link
2024-01-16 Initial fw support for lite version
2024-01-16 Fix missing features bitmap in EDID
2024-01-24 Update firmware for lite version
2024-01-26 r0p7 wip, check in before switch to kicad 8
2024-02-01 r0p7 wip
2024-02-04 Implement USB mux firmware support
2024-02-04 Add license notice for firmware
2024-02-04 Add support for 600x800 timing mode
2024-02-12 r0p7 layout done
2024-02-12 lite r0p1 schematic fixes
2024-02-13 Fix NPTH clearance issue
2024-02-15 Add dummy USB support
2024-02-15 Initial USB command implementation
2024-04-02 Add adapter for ED067KC1/ED113TC1; revise mainboard connector model
2024-04-05 USB interface proof-of-concept implementation
2024-04-28 Initial fw port to r0p7
2024-04-29 Add list of known screens
2024-04-29 Add a few notes in the screen list
2024-04-30 Initial driver support for ADV7611
2024-05-03 Fix PD for r0p7; Add config for 11.3 panel
2024-05-03 Rename old 39p adapter to 39p-a; Add 39p-c adapter
2024-05-03 Update screen list
2024-05-03 Rename 50p-adapater to 50p-adapater-a
2024-05-10 Bug fixes and changes for r0p8
2024-05-10 New adapters WIP
2024-05-13 Remove outdated diagram
2024-05-14 Fix wording
2024-05-14 Update ACeP story
2024-05-14 Additional Comments on ACeP
2024-05-14 Check in waveform tools
2024-05-15 Update title image
2024-05-15 Correct spelling mistakes
2024-05-15 Spelling fixes
2024-05-21 Add link to crowdsupply; add a few more screens
2024-05-25 Update adapters
2024-05-25 PCB r0p8
2024-05-28 Update on ACeP story
2024-06-15 Revise ADV settings, add new resolution presets
2024-06-23 Back port to r0p6
2024-06-24 Initial bring up USB HID interface
2024-07-04 Add EC097SC3
2024-07-04 BOM adjustments
2024-07-04 Update 39p-b adapter design
2024-07-04 General update, more discussion about color screens
2024-07-04 Add one more comparison photo
2024-07-04 Add photos for subpixel rendering
2024-07-04 Update info about 6in kaleido
2024-09-22 R0P9 PCB WIP
2024-11-19 Switch to use pcb_common submodule
2024-11-19 PCB r0p9
2024-12-17 Add info about 7.1in kaleido
2024-12-17 PCB r0p10 wip
2024-12-26 Add info for a few more panels
2024-12-26 Add info about XCA
2025-02-03 Add more panels to the list
2025-02-22 PCB r0p10
2025-02-22 Add tool for converting 5bpp wvfm to 4bpp
2025-04-15 New firmware for STM32 based controller
2025-04-25 Remove outdated boards
2025-04-25 PCB r0p13
2025-04-25 PCB r0p11
2025-05-08 Move usb example into utils
2025-05-19 Improve PD reliability
2025-05-19 Implement OSD feature
2025-05-19 Enable power monitoring
2025-05-19 Update information about adapters
2025-06-12 Add SN initial to the table
2025-06-26 PCB r1.1
2025-07-13 Add u133 adapter
2025-08-06 Use relative path for submodule
2025-08-06 PCB r1.2, new adapters
2025-08-06 Update changelist
2025-08-06 Implement support for uni-directional waveform in the dump tool
2025-08-06 Implement power up sequence check
2025-08-06 Add mirror into shell set_cfg variable list
2025-08-14 Add instructions for changing resolution
2025-08-14 Add more fail-safe protections; Change USB block size to 64
2025-08-14 Experimental flashing tool
2025-08-14 Update instructions for flashing firmware
2025-08-25 Rewrite nested f-string
2026-06-26 not a microHDMI, but a miniHDMI

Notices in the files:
fw/config.h:
Copyright 2023 Wenting Zhang <zephray@outlook.com>
README.md:
License:
This document, other than references explicitly given with their corresponding license, is released into the public domain.
The hardware design is released under the CERN Open Source Hardware License strongly-reciprocal variant, CERN-OHL-S. A copy of the license is provided in the source repository. Additionally, a user guide of the license is provided on ohwr.org.
The firmware code is licensed under the MIT license with the following exceptions: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
(Original illustration copyright MiHoYo)
